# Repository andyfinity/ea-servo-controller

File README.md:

# ExperimentalAvionics Servo Controller

A simple circuit board with just enough smarts to move a servo motor between two adjustable locations.

## About

This project evolved from the need to replace a mechanical actuator inside the engine cowling of a small, experimental airplane.

Position input can be given by a switch, a potentiometer, or an analog signal. Power input is anything from 6V to 18V. Since a switching regulator is used, a higher voltage implies lower current. Servo output is 5V at up to 2A, where the position signal is a 0.5ms to 2.5ms pulse every 20ms.

For your convenience, pinouts are displayed on the back of the PCB.

[Online BOM with vendor links.](https://octopart.com/bom-tool/hhvvhDB6)

## Contributing

[Atmel Studio 7](https://www.microchip.com/mplab/avr-support/atmel-studio-7) is used to compile the source code. [pyupdi](https://github.com/mraardvark/pyupdi/) is then used to push the .hex file to the ATtiny402.

The serial port can be any 3.3V UART-to-USB device, but we used [this one](https://www.tinyosshop.com/index.php?route=product/product&product_id=600). 5V will probably work, but it's untested.

PRs are welcome. There's not a lot of hand-written source code, so just make your edits look nice. If you make any changes to the PCB or schematic, make sure ERC and DRC come back mostly clean.

## License

Everything is released under the GPLv3.

## TODO

* Release the source code and .hex file
* Show pictures in README
* Design basic enclosure
* Release PCB STEP file
* Think about replacing the ATtiny with a bunch of discrete parts
* Think about increasing the 5V rail to 6V to increase motor speed

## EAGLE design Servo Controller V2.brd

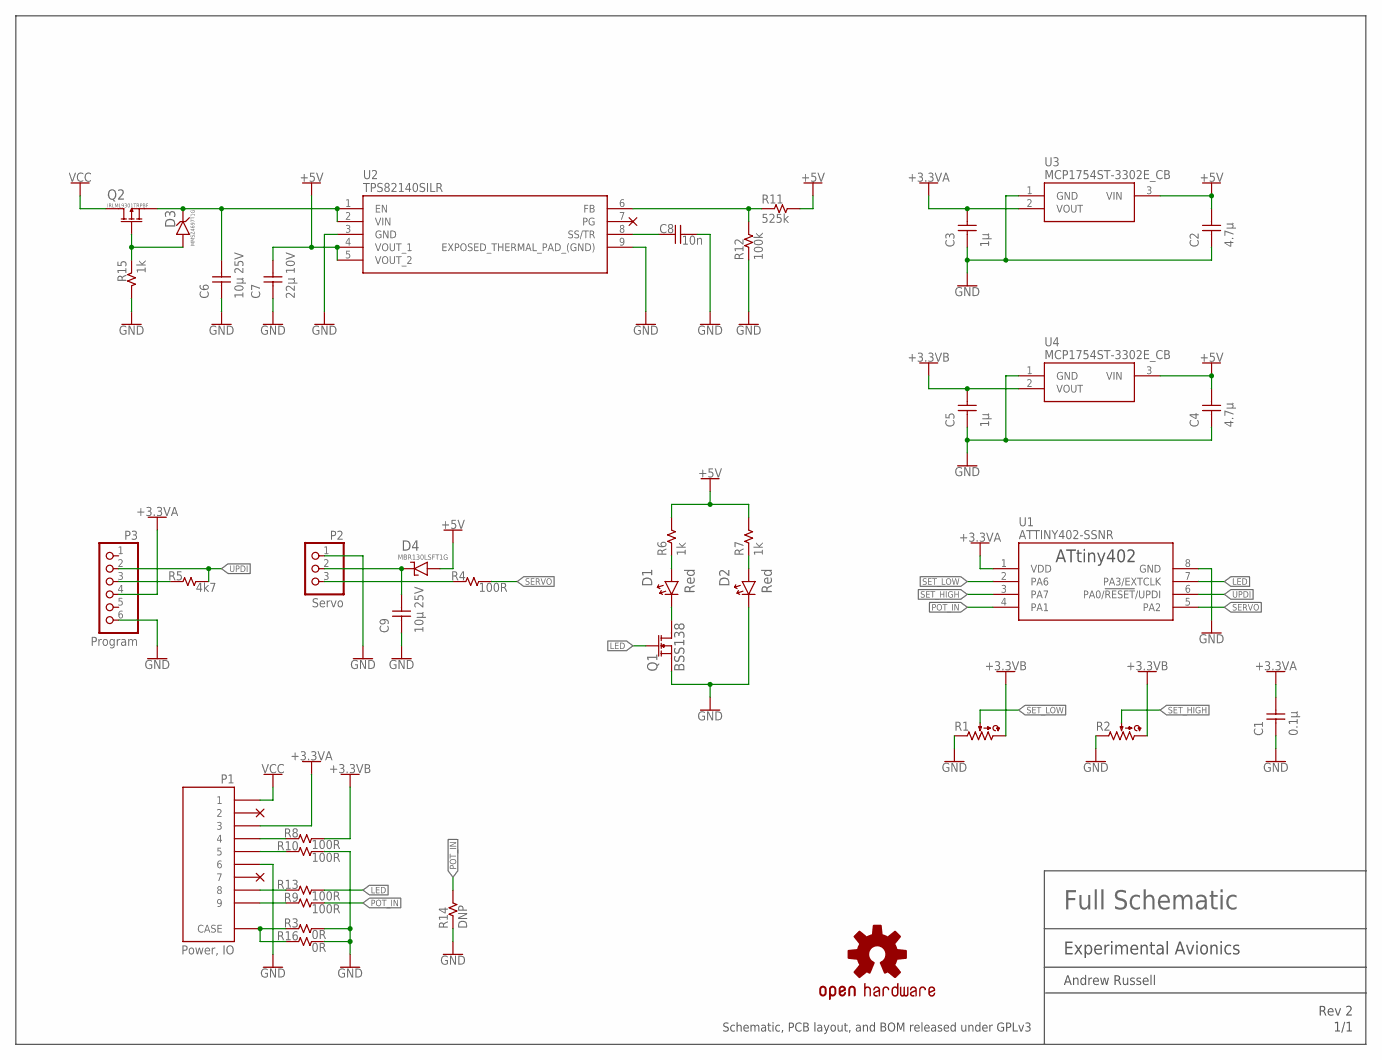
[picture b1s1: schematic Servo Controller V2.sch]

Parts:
C1: 0.1µ; CAPC1608X90
C2, C4: 4.7µ; CAPC2012X90
C3, C5: 1µ; CAPC2012X90
C6, C9: 10µ 25V; CAPC3216X180
C7: 22µ 10V; CAPC2012X90
C8: 10n; CAPC1608X90
D1, D2: Red; SODFL3216X68
D3: MMSZ4697T1G; SODFL3518X115
D4: MBR130LSFT1G; SODFL3616X98
LOGO1: OSHW-LOGOMINI; OSHW-LOGO-MINI
P1: Power, IO; D09P24A4GV00LF
P2: Servo; 1X03/90
P3: Program; 1X06
Q1: BSS138; SOT95P240X110-3
Q2: IRLML9301TRPBF; SOT95P240X110-3
R1, R2: POTENTIOMETER; TT_23B
R3, R16: 0R; RESC1608X55
R4, R8, R9, R10, R13: 100R; RESC1608X55
R5: 4k7; RESC1608X55
R6, R7, R15: 1k; RESC1608X55
R11: 525k; RESC1608X55
R12: 100k; RESC1608X55
R14: DNP; RESC1608X55
U1: ATTINY402-SSNR; SOIC127P599X175-8
U2: TPS82140SILR; SIL0008D
U3, U4: MCP1754ST-3302E_CB; SOT95P255X145-3N

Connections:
+3V3A: C1.2, C3.2, P1.P$3 (3), P3.4, U1.1 (VDD), U3.2 (VOUT)
+3V3B: C5.2, R1.P$3, R2.P$3, R8.2, U4.2 (VOUT)
+5V: C2.2, C4.2, C7.2, D4.2 (A), R6.2, R7.2, R11.2, U2.4 (VOUT_1), U2.5 (VOUT_2), U3.3 (VIN), U4.3 (VIN)
GND: C1.1, C2.1, C3.1, C4.1, C5.1, C6.1, C7.1, C8.2, C9.1, D2.1 (C), P1.P$6 (6), P2.1, P3.6, Q1.2 (S), R1.P$1, R2.P$1, R3.2, R10.2, R12.1, R14.1, R15.2, R16.2, U1.8 (GND), U2.3 (GND), U2.9 (EXPOSED_THERMAL_PAD_(GND)), U3.1 (GND), U4.1 (GND)
LED: Q1.1 (G), R13.2, U1.7 (PA3/EXTCLK)
unnamed: P3.3, R5.1
unnamed: C8.1, U2.8 (SS/TR)
unnamed: P1.P$10 (CASE), P1.P$11 (CASE), R3.1, R16.1
unnamed: D1.2 (A), R6.1
unnamed: R11.1, R12.2, U2.6 (FB)
unnamed: P1.P$9 (9), R9.1
unnamed: P1.P$5 (5), R10.1
unnamed: D2.2 (A), R7.1
unnamed: D1.1 (C), Q1.3 (D)
unnamed: P2.3, R4.1
unnamed: P1.P$4 (4), R8.1
unnamed: P1.P$8 (8), R13.1
unnamed: D3.2 (A), Q2.1 (G), R15.1
unnamed: C6.2, D3.1 (C), Q2.2 (S), U2.1 (EN), U2.2 (VIN)
unnamed: C9.2, D4.1 (C), P2.2
POT_IN: R9.2, R14.2, U1.4 (PA1)
SERVO: R4.2, U1.5 (PA2)
SET_HIGH: R2.P$2, U1.3 (PA7)
SET_LOW: R1.P$2, U1.2 (PA6)
UPDI: P3.2, R5.2, U1.6 (PA0/!RESET!/UPDI)
VCC: P1.P$1 (1), Q2.3 (D)

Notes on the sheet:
Schematic, PCB layout, and BOM released under GPLv3

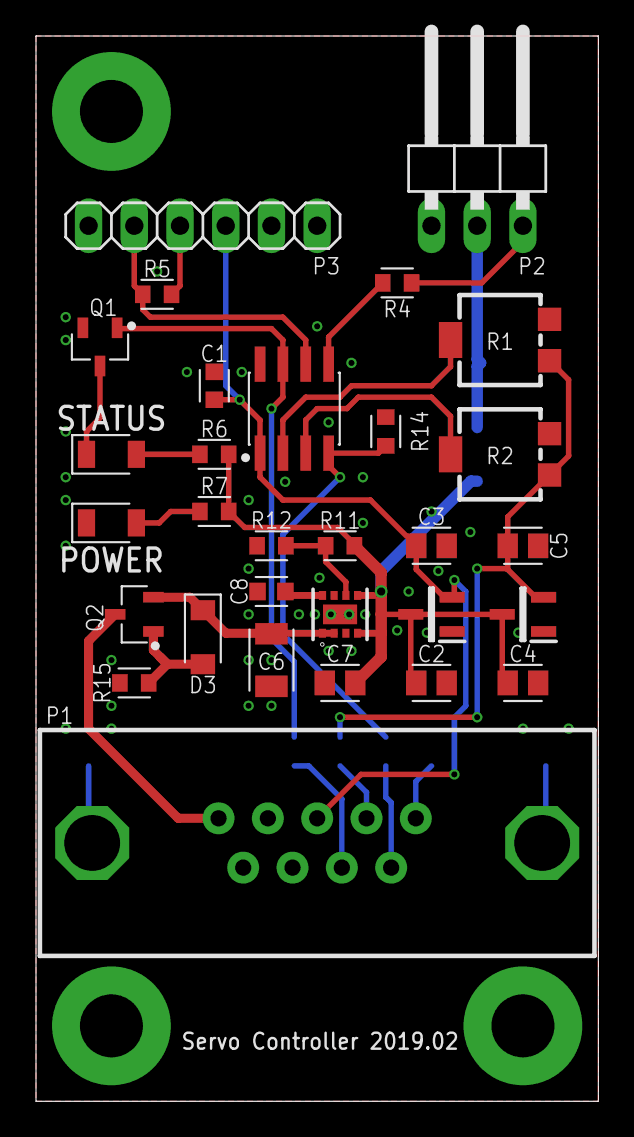
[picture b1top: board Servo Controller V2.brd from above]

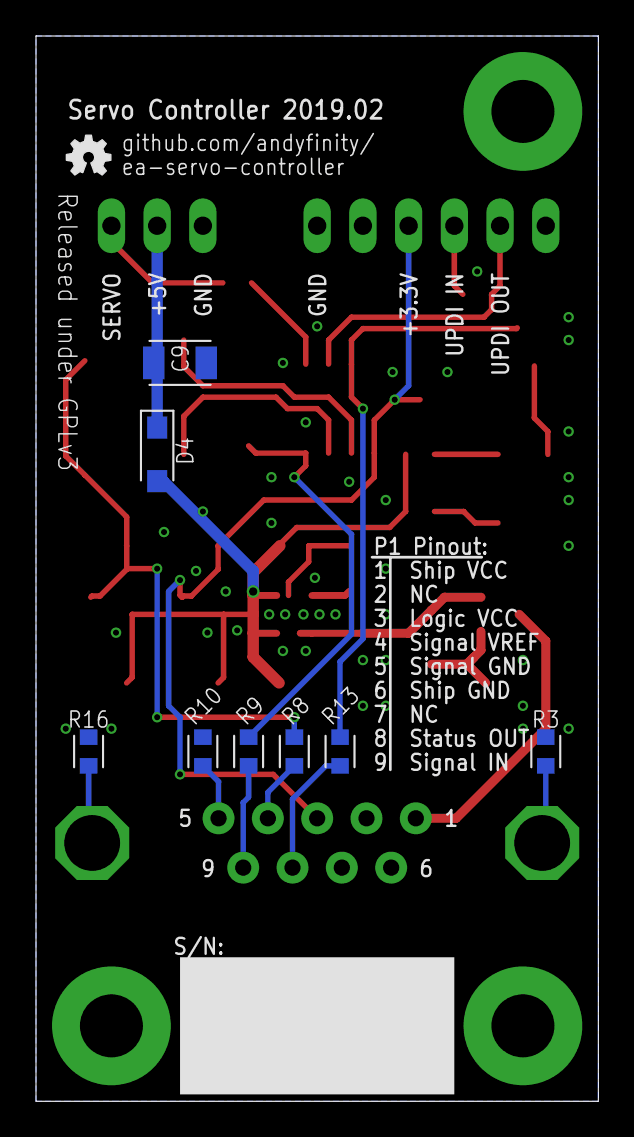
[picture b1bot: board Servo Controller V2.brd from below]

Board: 2 copper layers, 31.2 x 59.2 mm, 39 parts (9 on the bottom side), 26 nets.

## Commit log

2019-02-25 Initial release
2019-03-06 Eliminated back EMI on the 5V rail from a large motor braking.
2019-03-06 Display OSHW logo on schematic.

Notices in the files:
parts and their libraries:
SparkFun-Aesthetics: Licensing: Creative Commons ShareAlike 4.0 International - https://creativecommons.org/licenses/by-sa/4.0
